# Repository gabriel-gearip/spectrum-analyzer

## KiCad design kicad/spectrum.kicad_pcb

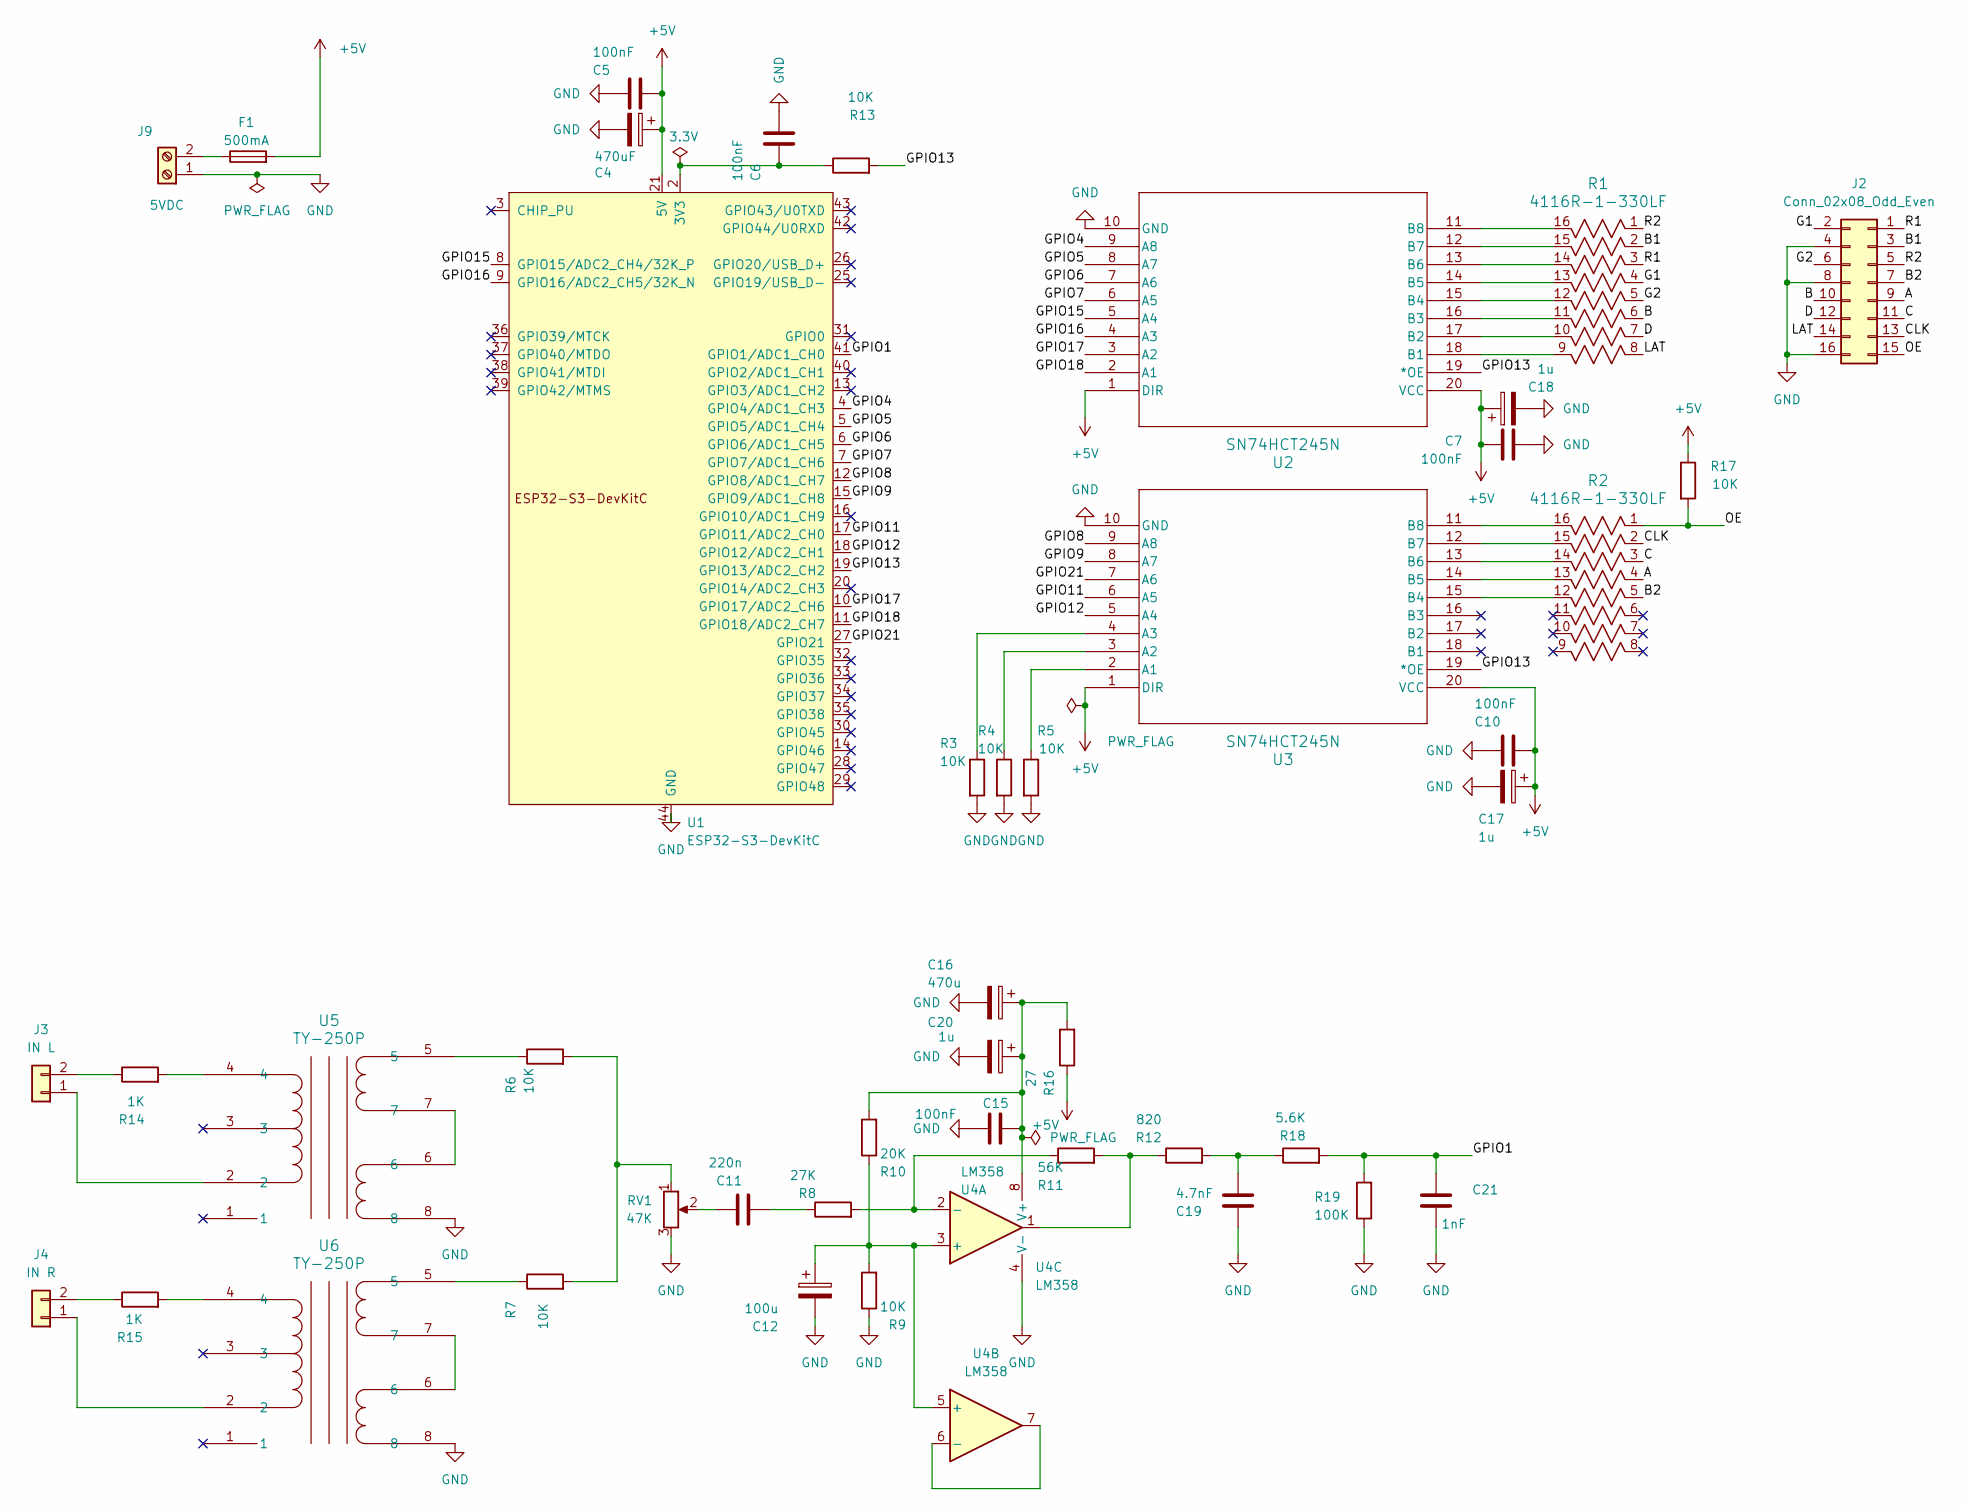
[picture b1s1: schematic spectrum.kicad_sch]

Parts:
C4: 470uF; CP_Radial_D8.0mm_P3.50mm
C5, C6, C7, C10, C15: 100nF; C_Disc_D3.4mm_W2.1mm_P2.50mm
C11: 220n; C_Rect_L7.2mm_W3.0mm_P5.00mm_FKS2_FKP2_MKS2_MKP2
C12: 100u; CP_Radial_D5.0mm_P2.00mm
C16: 470u; CP_Radial_D8.0mm_P3.50mm
C17, C18, C20: 1u; C_Disc_D4.7mm_W2.5mm_P5.00mm
C19: 4.7nF; C_Rect_L7.2mm_W3.0mm_P5.00mm_FKS2_FKP2_MKS2_MKP2
C21: 1nF; C_Rect_L7.2mm_W3.0mm_P5.00mm_FKS2_FKP2_MKS2_MKP2
F1: 500mA; Fuseholder_Clip-5x20mm_Littelfuse_445-030_Inline_P20.50x5.2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
J2: Conn_02x08_Odd_Even; IDC-Header_2x08_P2.54mm_Vertical
J3: IN L; JST_XH_B2B-XH-A_1x02_P2.50mm_Vertical
J4: IN R; JST_XH_B2B-XH-A_1x02_P2.50mm_Vertical
J9: 5VDC; Conector_Verde_2_pini
R1, R2: 4116R-1-330LF; DIP-16_W7.62mm
R3, R4, R5, R6, R7, R9, R13, R17: 10K; R_Axial_DIN0207_L6.3mm_D2.5mm_P10.16mm_Horizontal
R8: 27K; R_Axial_DIN0207_L6.3mm_D2.5mm_P10.16mm_Horizontal
R10: 20K; R_Axial_DIN0207_L6.3mm_D2.5mm_P10.16mm_Horizontal
R11: 56K; R_Axial_DIN0207_L6.3mm_D2.5mm_P10.16mm_Horizontal
R12: 820; R_Axial_DIN0207_L6.3mm_D2.5mm_P10.16mm_Horizontal
R14, R15: 1K; R_Axial_DIN0207_L6.3mm_D2.5mm_P10.16mm_Horizontal
R16: 27; R_Axial_DIN0207_L6.3mm_D2.5mm_P10.16mm_Horizontal
R18: 5.6K; R_Axial_DIN0207_L6.3mm_D2.5mm_P10.16mm_Horizontal
R19: 100K; R_Axial_DIN0207_L6.3mm_D2.5mm_P10.16mm_Horizontal
RV1: 47K; Potentiometer_Runtron_RM-065_Vertical
U1: ESP32-S3-DevKitC
U2, U3: SN74HCT245N; N20
U4: LM358; DIP-8_W7.62mm
U5, U6: TY-250P; TO_250P_TRM

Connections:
+5V: C4.1, C5.2, C7.2, C10.2, C17.1, C18.1, F1.2, R16.1, R17.1, U1.21 (5V), U2.1 (DIR), U2.20 (VCC), U3.1 (DIR), U3.20 (VCC)
/A: J2.9, R2.4
/B: J2.10, R1.6
/B1: J2.3, R1.2
/B2: J2.7, R2.5
/C: J2.11, R2.3
/CLK: J2.13, R2.2
/D: J2.12, R1.7
/G1: J2.2, R1.4
/G2: J2.6, R1.5
/GPIO1: C21.2, R18.2, R19.2, U1.41 (GPIO1/ADC1_CH0)
/GPIO4: U1.4 (GPIO4/ADC1_CH3), U2.9 (A8)
/GPIO5: U1.5 (GPIO5/ADC1_CH4), U2.8 (A7)
/GPIO6: U1.6 (GPIO6/ADC1_CH5), U2.7 (A6)
/GPIO7: U1.7 (GPIO7/ADC1_CH6), U2.6 (A5)
/GPIO8: U1.12 (GPIO8/ADC1_CH7), U3.9 (A8)
/GPIO9: U1.15 (GPIO9/ADC1_CH8), U3.8 (A7)
/GPIO11: U1.17 (GPIO11/ADC2_CH0), U3.6 (A5)
/GPIO12: U1.18 (GPIO12/ADC2_CH1), U3.5 (A4)
/GPIO13: R13.2, U1.19 (GPIO13/ADC2_CH2), U2.19 (*OE), U3.19 (*OE)
/GPIO15: U1.8 (GPIO15/ADC2_CH4/32K_P), U2.5 (A4)
/GPIO16: U1.9 (GPIO16/ADC2_CH5/32K_N), U2.4 (A3)
/GPIO17: U1.10 (GPIO17/ADC2_CH6), U2.3 (A2)
/GPIO18: U1.11 (GPIO18/ADC2_CH7), U2.2 (A1)
/GPIO21: U1.27 (GPIO21), U3.7 (A6)
/LAT: J2.14, R1.8
/OE: J2.15, R2.1, R17.2
/R1: J2.1, R1.3
/R2: J2.5, R1.1
GND: C4.2, C5.1, C6.2, C7.1, C10.1, C12.2, C15.1, C16.2, C17.2, C18.2, C19.2, C20.2, C21.1, J2.4, J2.8, J2.16, J9.1, R3.2, R4.2, R5.2, R9.1, R19.1, RV1.3, U1.22 (GND), U1.23 (GND), U1.24 (GND), U1.44 (GND), U2.10 (GND), U3.10 (GND), U4.4 (V-), U5.8, U6.8
unnamed: C6.1, R13.1, U1.1 (3V3), U1.2 (3V3)
unnamed: C11.1, RV1.2
unnamed: C11.2, R8.1
unnamed: C19.1, R12.2, R18.1
unnamed: J3.1, U5.2
unnamed: J3.2, R14.1
unnamed: J4.1, U6.2
unnamed: J4.2, R15.1
unnamed: F1.1, J9.2
unnamed: R6.1, U5.5
unnamed: R6.2, R7.2, RV1.1
unnamed: R7.1, U6.5
unnamed: R11.2, R12.1, U4.1
unnamed: R14.2, U5.4
unnamed: R15.2, U6.4
unnamed: R1.9, U2.18 (B1)
unnamed: R1.10, U2.17 (B2)
unnamed: R1.11, U2.16 (B3)
unnamed: R1.12, U2.15 (B4)
unnamed: R1.13, U2.14 (B5)
unnamed: R1.14, U2.13 (B6)
unnamed: R1.15, U2.12 (B7)
unnamed: R1.16, U2.11 (B8)
unnamed: R5.1, U3.2 (A1)
unnamed: R4.1, U3.3 (A2)
unnamed: R3.1, U3.4 (A3)
unnamed: R2.12, U3.15 (B4)
unnamed: R2.13, U3.14 (B5)
unnamed: R2.14, U3.13 (B6)
unnamed: R2.15, U3.12 (B7)
unnamed: R2.16, U3.11 (B8)
unnamed: C12.1, R9.2, R10.1, U4.3 (+), U4.5 (+)
unnamed: R8.2, R11.1, U4.2 (-)
unnamed: U4.6 (-), U4.7
unnamed: C15.2, C16.1, C20.1, R10.2, R16.2, U4.8 (V+)
unnamed: U5.6, U5.7
unnamed: U6.6, U6.7

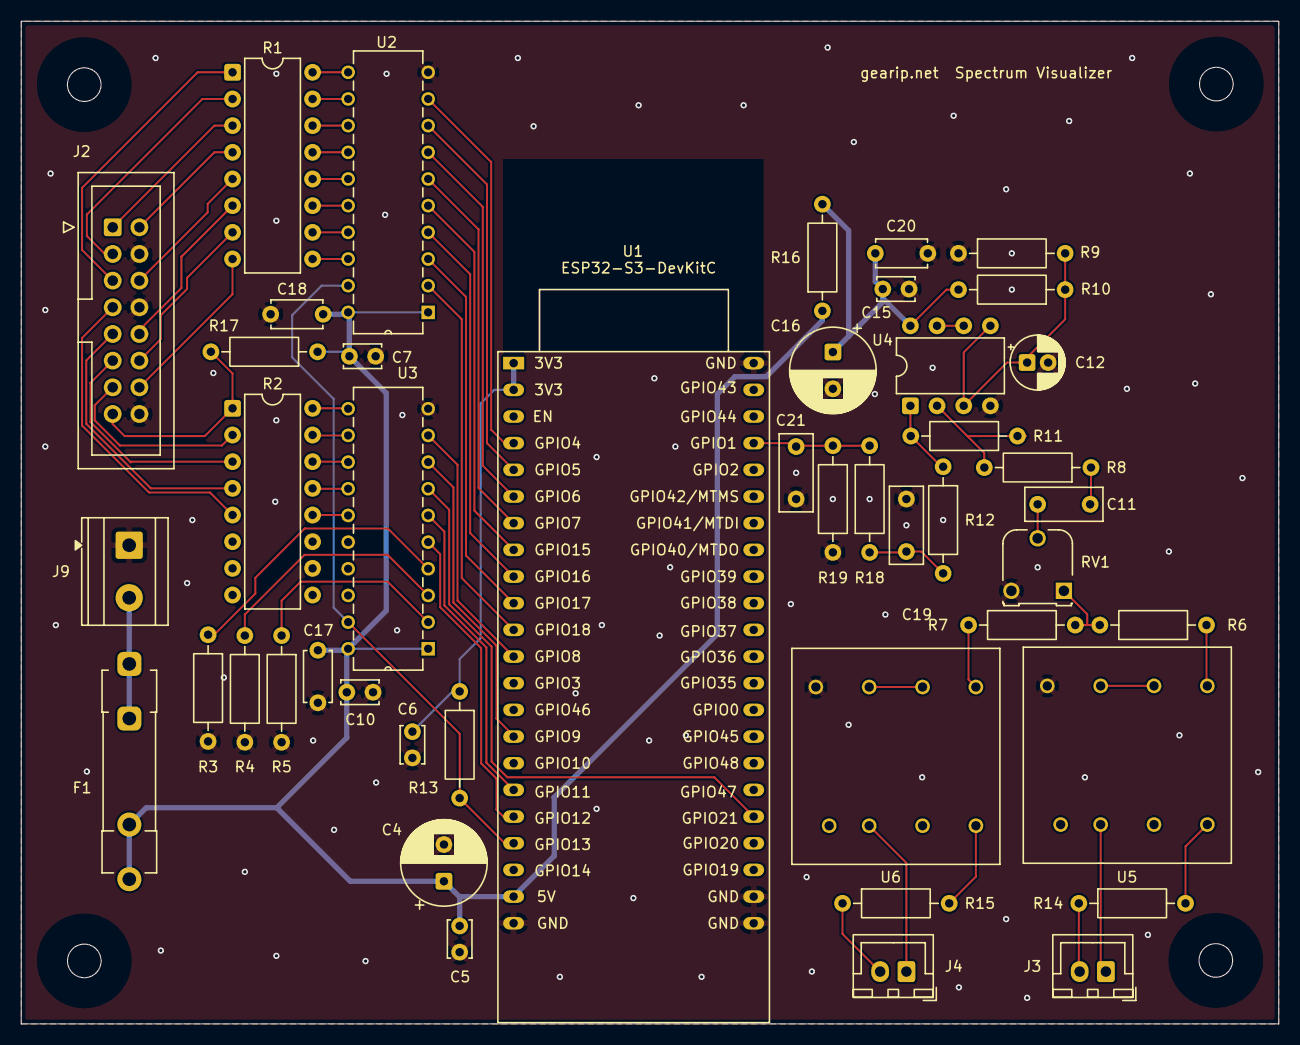
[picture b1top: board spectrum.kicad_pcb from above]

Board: 2 copper layers, 119.7 x 95.5 mm, 45 parts (0 on the bottom side), 67 nets.
